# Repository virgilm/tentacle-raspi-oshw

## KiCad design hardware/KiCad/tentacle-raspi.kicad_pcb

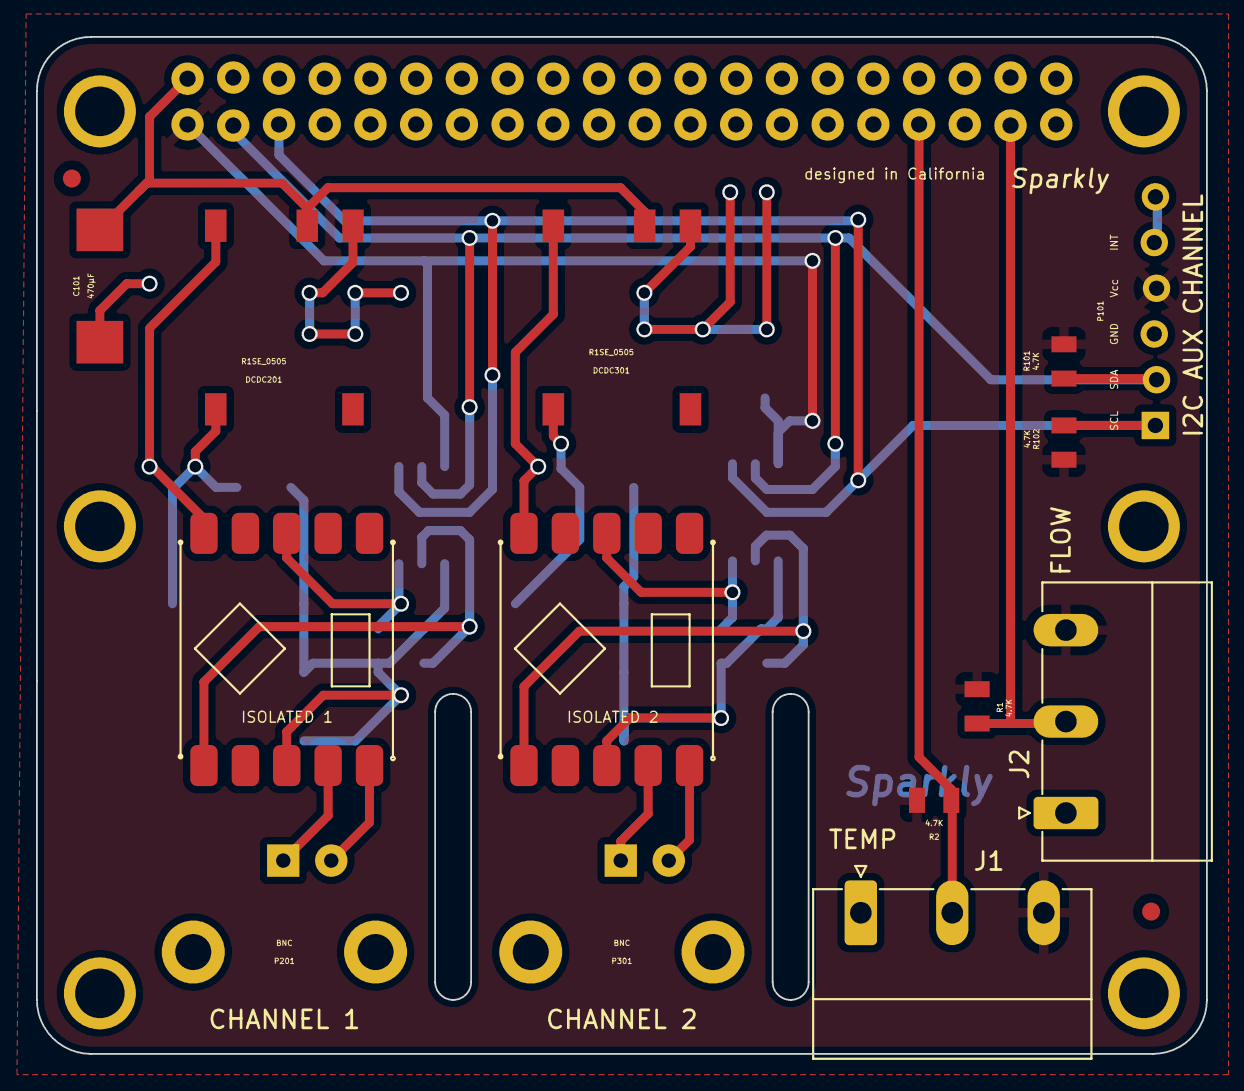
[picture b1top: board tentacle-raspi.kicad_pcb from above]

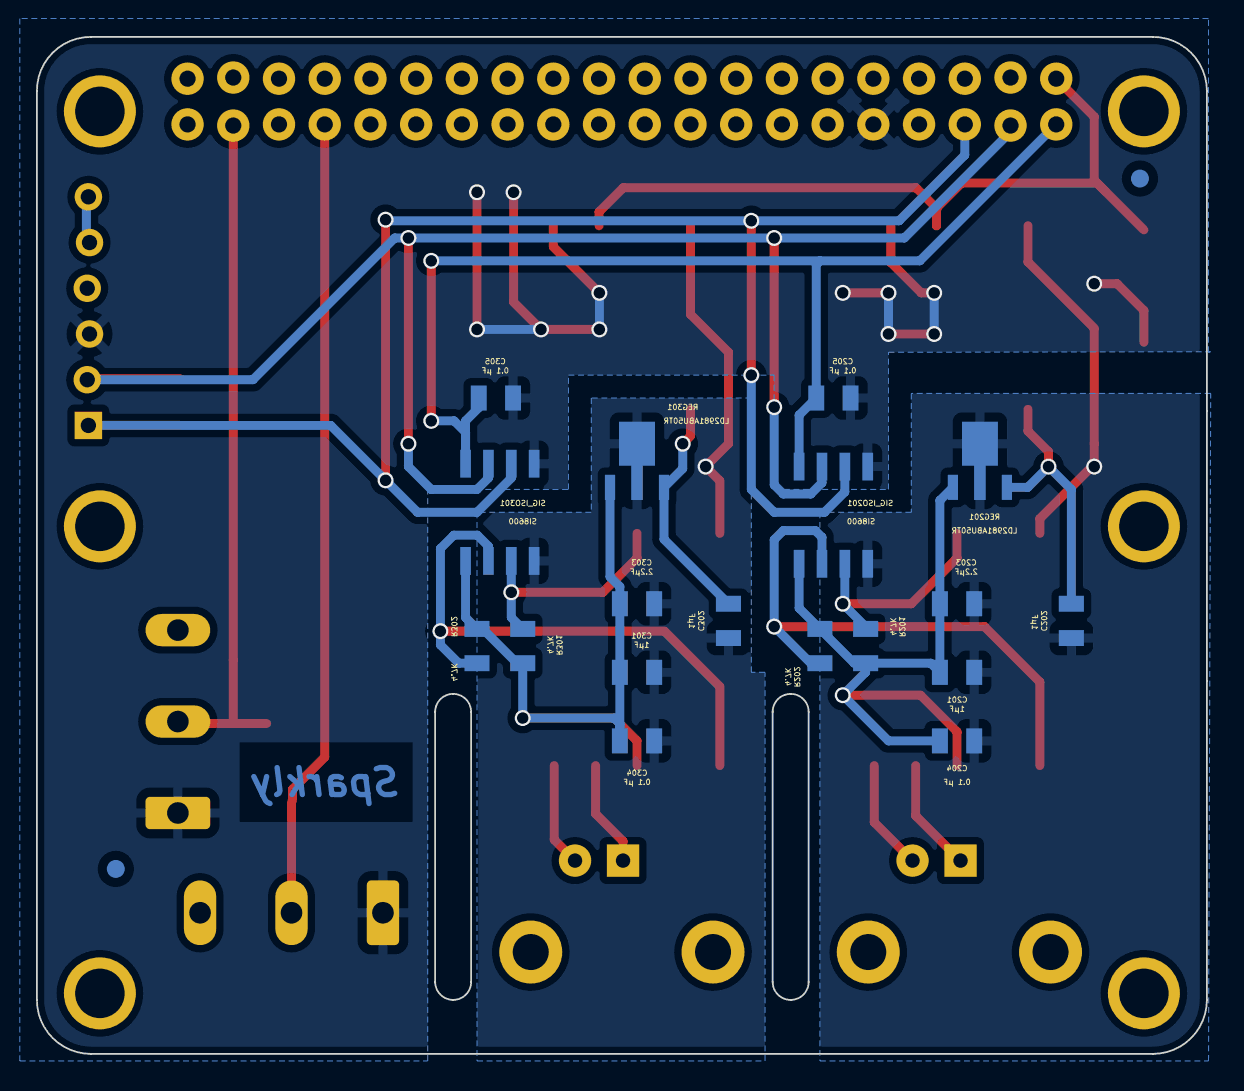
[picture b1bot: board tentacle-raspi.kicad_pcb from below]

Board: 2 copper layers, 65.0 x 56.5 mm, 38 parts (20 on the bottom side), 22 nets.

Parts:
C101: 470µF; WL-CASE-X-2917
C201, C202, C301, C302: 1µF; WL-SM0805C
C203, C303: 2.2µF; WL-SM0805C
C204, C205, C304, C305: 0.1 µF; WL-SM0805C
DCDC201, DCDC301: R1SE_0505; WL-R1SE-0505
J1, J2: Conn_01x03; PhoenixContact_MC_1,5_3-G-5.08_1x03_P5.08mm_Horizontal
P101: CONN_01X06; WL-PINH_1X6_snk
P201, P301: BNC; WL-EB08040502_snk
PI_BOARD101: RASPBERRY_PI_2; WL-40pin_snk
PI_Board: VAL**; WL-PI_Board_no_outline
R1, R2, R101, R102, R201, R202, R301, R302: 4.7K; WL-SM0805R
REG201, REG301: LD2981ABU50TR; WL-SOT89
SIG_ISO201, SIG_ISO301: SI8600; WL-SOIC8N
STP201, STP301: EZO_SMD; WL-ezo-smd
fiducial: VAL**; WL-fiducial_1mm
fiducial#2, fiducial#3, fiducial#4: VAL**; WL-fiducial_1mm

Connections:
+3.3V: C205.1, C305.1, J1.3, J2.3, P101.4, PI_BOARD101.1 (3.3v), R1.2, R2.2, R101.2, R102.2, SIG_ISO201.8 (BVCC), SIG_ISO301.8 (BVCC)
/SCL: P101.1, PI_BOARD101.5 (GPIO03_(SCL_I2C)), R102.1, SIG_ISO201.6 (BSCL), SIG_ISO301.6 (BSCL)
/SDA: P101.2, PI_BOARD101.3 (GPIO02_(SDA_I2C)), R101.1, SIG_ISO201.7 (BSDA), SIG_ISO301.7 (BSDA)
/nonisolated1/FLOW: J2.2, PI_BOARD101.37 (GPIO26), R1.1
/nonisolated1/TEMP: J1.2, PI_BOARD101.33 (GPIO13), R2.1
GND: C101.2, C205.2, C305.2, DCDC201.1 (GND), DCDC301.1 (GND), J1.1, J2.1, P101.3, PI_BOARD101.9 (Ground), SIG_ISO201.5 (BGND), SIG_ISO301.5 (BGND)
GND_ISO2: C201.1, C202.1, C203.1, C204.1, DCDC201.4 (GND_ISO), REG201.2 (GND), SIG_ISO201.4 (AGND), STP201.6 (GND)
GND_ISO3: C301.1, C302.1, C303.1, C304.1, DCDC301.4 (GND_ISO), REG301.2 (GND), SIG_ISO301.4 (AGND), STP301.6 (GND)
unnamed: C202.2, DCDC201.5 (V_ISO), REG201.3 (Vin)
unnamed: C302.2, DCDC301.5 (V_ISO), REG301.3 (Vin)
unnamed: P101.5, P101.6
unnamed: P201.1 (In), STP201.4 (PRB)
unnamed: P201.2 (Ext), STP201.5 (PRB_GND)
unnamed: P301.1 (In), STP301.4 (PRB)
unnamed: P301.2 (Ext), STP301.5 (PRB_GND)
unnamed: R201.2, SIG_ISO201.3 (ASCL), STP201.8 (SCL)
unnamed: R202.2, SIG_ISO201.2 (ASDA), STP201.1 (SDA)
unnamed: R301.2, SIG_ISO301.3 (ASCL), STP301.8 (SCL)
unnamed: R302.2, SIG_ISO301.2 (ASDA), STP301.1 (SDA)
VCC: C101.1, DCDC201.2 (VCC), DCDC301.2 (VCC), PI_BOARD101.2 (5v)
V_ISO2: C201.2, C203.2, C204.2, R201.1, R202.1, REG201.1 (Vout), SIG_ISO201.1 (AVCC), STP201.3 (VCC)
V_ISO3: C301.2, C303.2, C304.2, R301.1, R302.1, REG301.1 (Vout), SIG_ISO301.1 (AVCC), STP301.3 (VCC)

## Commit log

2022-01-13 Modified to use OEM sensors.
    Moved most components to the other side.
    Created a new symbol and footprint.
2022-02-03 Version 2.0
    1wire sensor
    flow sensor
2022-02-06 V3, 1wire Temp sensor and flow sensor.
2022-08-16 V4
    - Corrected GND issue.
    - Separate PRB GND.
    - Enlarged J1,J2 holes to 1.3mm from 1.2mm
